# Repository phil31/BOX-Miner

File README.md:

## BOX Miner

#### The EKO-Miner is a stackable and rackable ASIC Bitcoin miner that utilizes hashcards. The hashcards are capable of mining Bitcoin by themselves or multiple. The concept of hashcards is highly scalable and offers a clean and streamlined approach to Bitcoin mining.

Miner Box Supports up to 3 ASIC Hashcards. An ATX PSU is required.

- Rackable miner boards based on specifics ASIC Hashboards, generic power supply and driven by an ESP32
- WIFI and ETHERNET connectivity
- TFT RGB LCD 172x320 display
- External standard ATX power supply
- Watercooling for quiet operation
- enclosure box dimensions: 200 x 200 x 140 mm

#### Power board : 
- designed with TPS53667 / 5 Phases / 0.5 to 2.5V, up to 380Watts
- 6 layers PCB - Outer / Inner Copper Weight: 2 oz

#### AsicBoards : 
- 16 x BM1366 : 8 TH/s - Efficiency 25J/TH
- 16 x BM1368 : 9.5 TH/s - Efficiency 18J/TH
- 10 x BM1370 : 12 TH/s - Efficiency 15J/TH

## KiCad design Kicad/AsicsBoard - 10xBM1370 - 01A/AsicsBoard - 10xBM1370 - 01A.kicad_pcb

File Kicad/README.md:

## BOX Miner

#### The EKO-Miner is a stackable and rackable ASIC Bitcoin miner that utilizes hashcards. The hashcards are capable of mining Bitcoin by themselves or multiple. The concept of hashcards is highly scalable and offers a clean and streamlined approach to Bitcoin mining.

#### 2024-12-07 : Theses boards are currently being validated

Power board : 
- designed with TPS53667 / 5 Phases / 0.5 to 2.5V, up to 300Watts

AsicBoards : 
- 16 x BM1366 : 8 TH/s - Efficiency 25J/TH
- 16 x BM1368 : 9.5 TH/s - Efficiency 18J/TH
- 10 x BM1370 : 10 TH/s - Efficiency 15J/TH

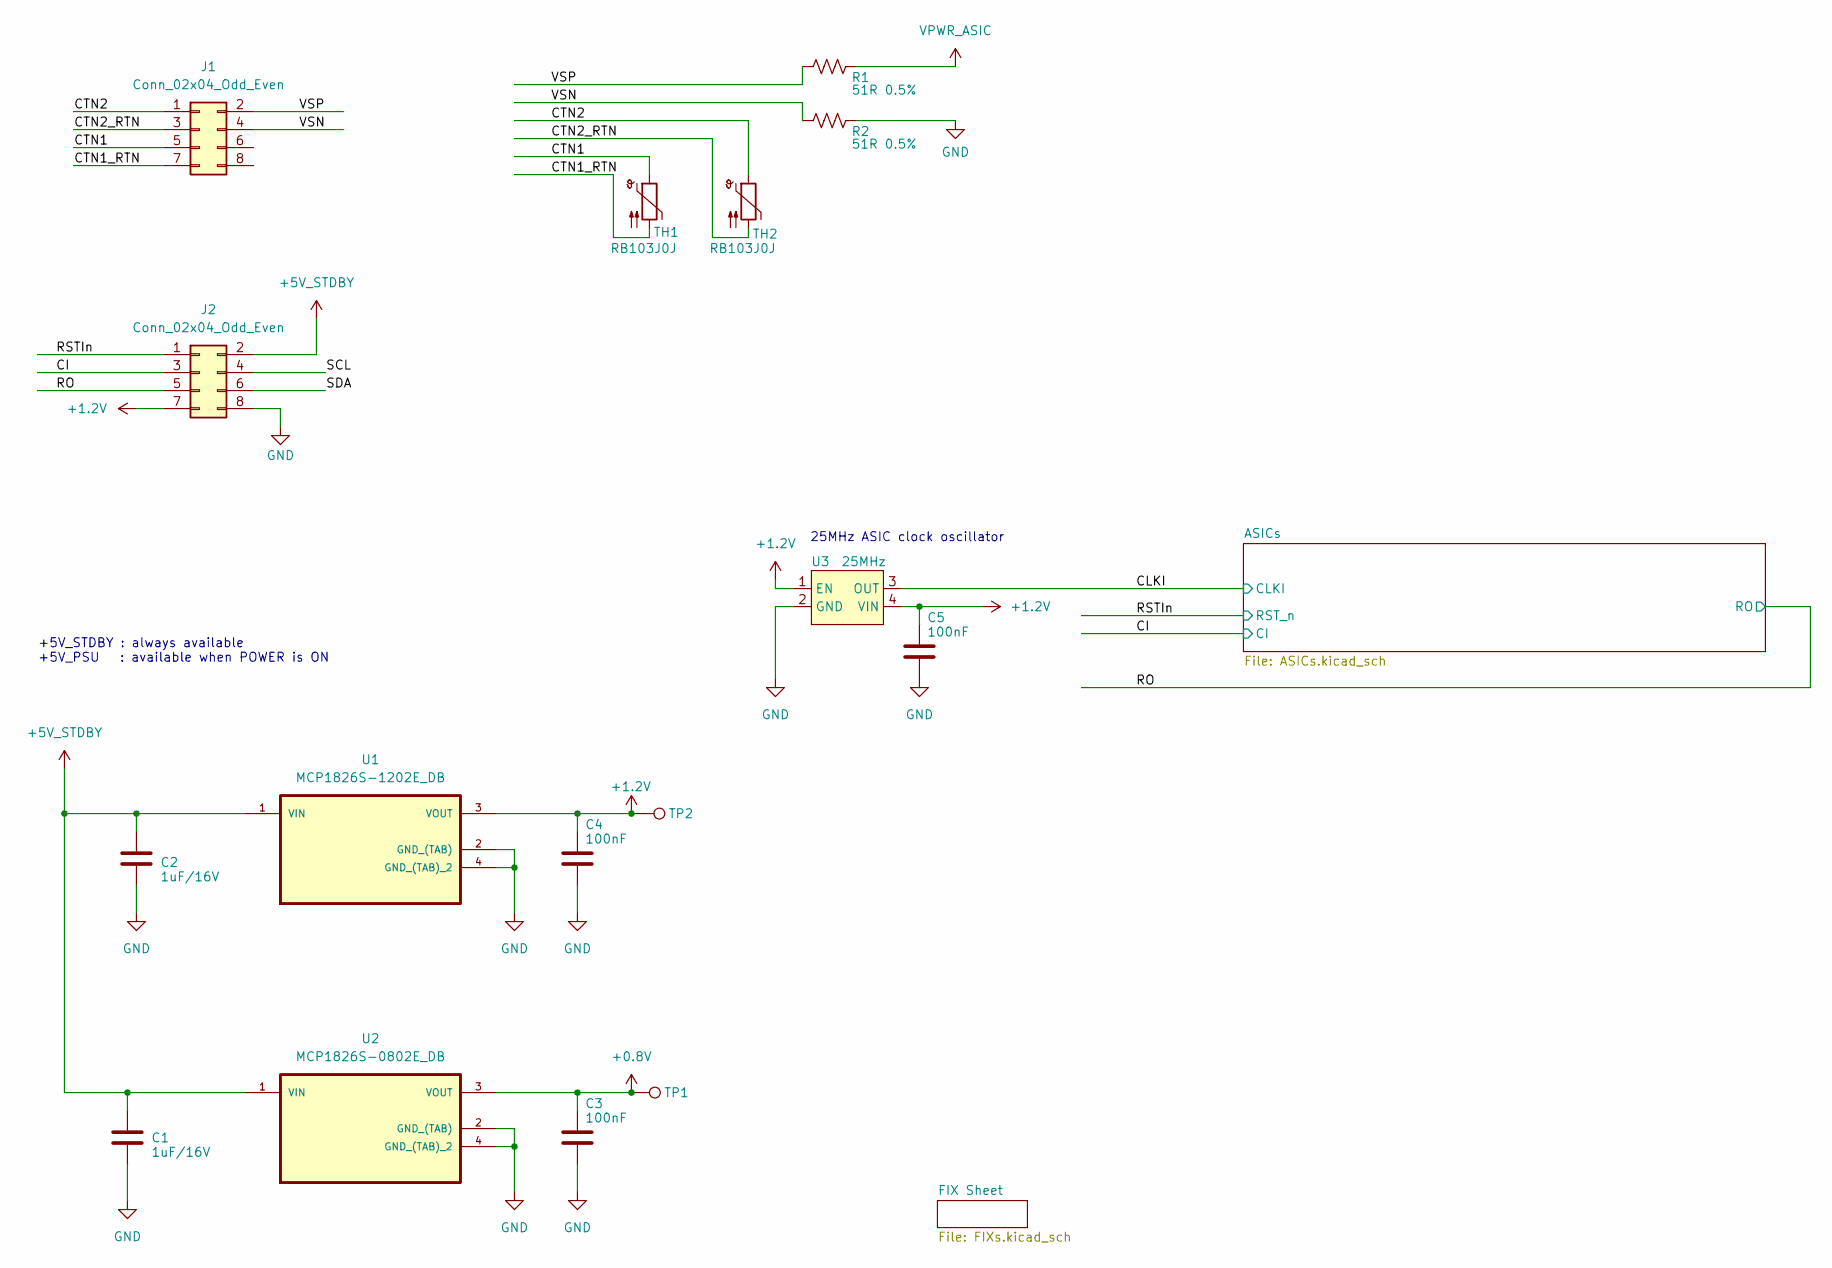
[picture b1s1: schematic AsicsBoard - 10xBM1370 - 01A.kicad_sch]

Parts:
C1, C2: 1uF/16V; C_0805_2012Metric_Pad1.18x1.45mm_HandSolder
C3, C4, C5: 100nF; C_0402_1005Metric
J1, J2: Conn_02x04_Odd_Even; PinHeader_2x04_P2.54mm_Vertical_SMD
R1, R2: 51R 0.5%; R_0805_2012Metric_Pad1.20x1.40mm_HandSolder
TH1, TH2: RB103J0J; R_0603_1608Metric
TP1, TP2: TestPoint; TestPoint_Pad_D1.0mm
U1: MCP1826S-1202E_DB; MCP1826S
U2: MCP1826S-0802E_DB; MCP1826S
U3: 25MHz; OSC_SMD_3.2x2.5mm

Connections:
+0.8V: C3.1, TP1.1, U2.3 (VOUT); also elsewhere on the board
+1.2V: C4.1, C5.1, J2.7, TP2.1, U1.3 (VOUT), U3.1 (EN), U3.4 (VIN); also elsewhere on the board
+5V_STDBY: C1.1, C2.1, J2.2, U1.1 (VIN), U2.1 (VIN)
/CI: J2.3; also elsewhere on the board
/CLKI: U3.3 (OUT); also elsewhere on the board
/CTN1: J1.5, TH1.1
/CTN1_RTN: J1.7, TH1.2
/CTN2: J1.1, TH2.1
/CTN2_RTN: J1.3, TH2.2
/RO: J2.5; also elsewhere on the board
/RSTIn: J2.1; also elsewhere on the board
/SCL: J2.4
/SDA: J2.6
/VSN: J1.4, R2.2
/VSP: J1.2, R1.2
GND: C1.2, C2.2, C3.2, C4.2, C5.2, J2.8, R2.1, U1.2 (GND_(TAB)), U1.4 (GND_(TAB)_2), U2.2 (GND_(TAB)), U2.4 (GND_(TAB)_2), U3.2 (GND); also elsewhere on the board
VPWR_ASIC: R1.1; also elsewhere on the board

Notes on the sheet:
+5V_STDBY : always available +5V_PSU : available when POWER is ON
25MHz ASIC clock oscillator

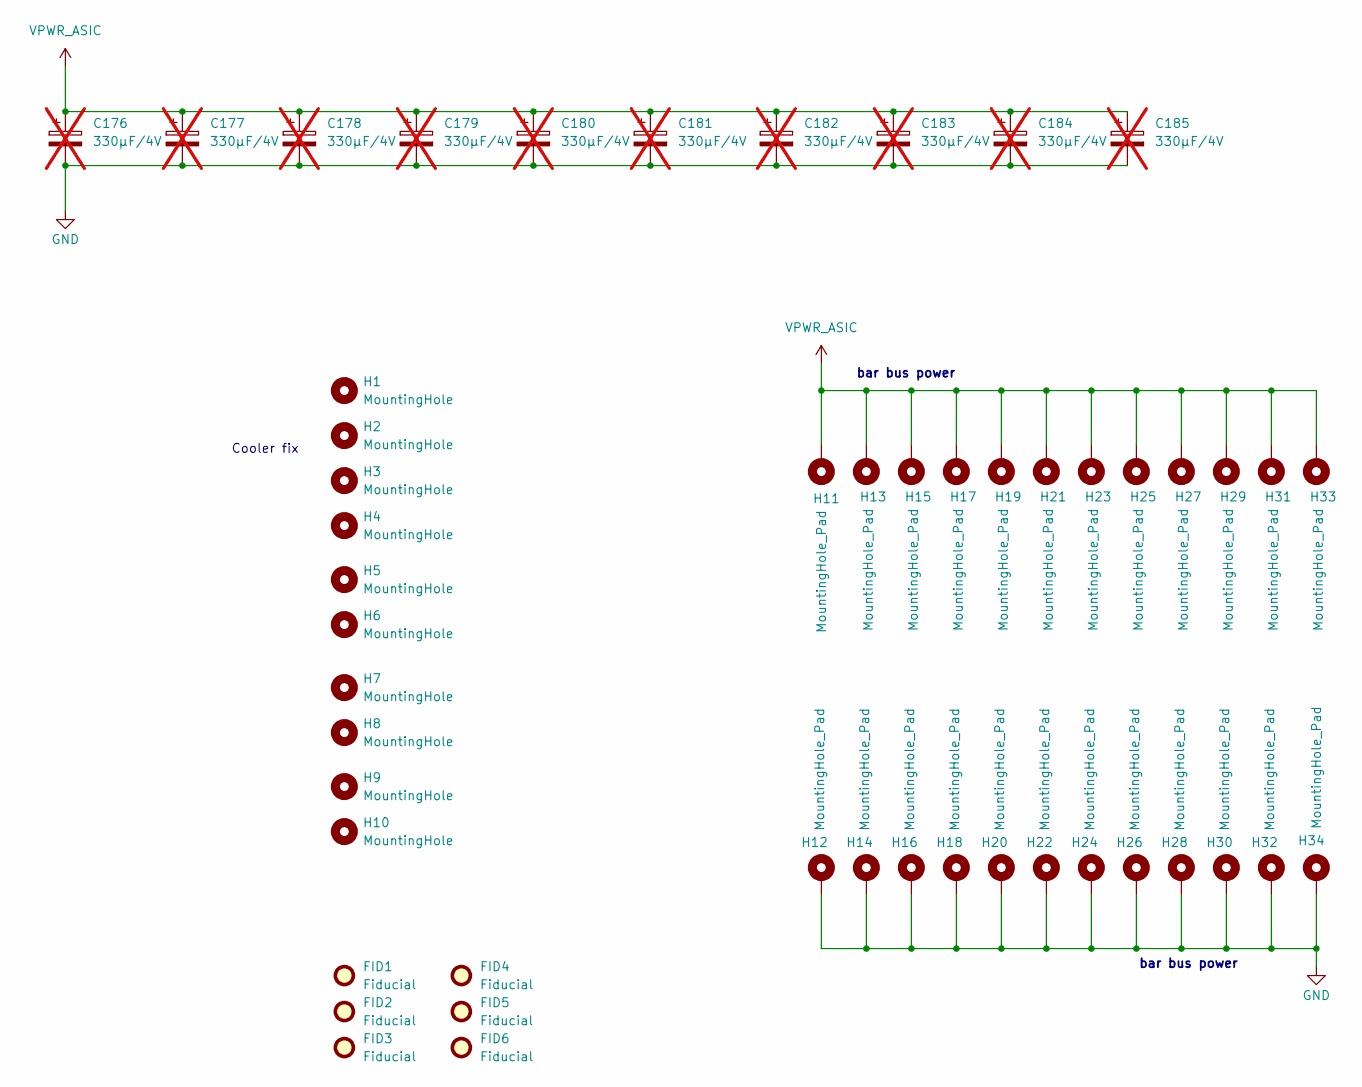
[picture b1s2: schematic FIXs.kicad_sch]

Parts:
C176, C177, C178, C179, C180, C181, C182, C183, C184, C185: 330µF/4V; C_1210_3225Metric; not fitted
FID1, FID2, FID3, FID4, FID5, FID6: Fiducial; Fiducial_1mm_Mask2mm
H1, H2, H3, H4, H5, H6, H7, H8, H9, H10: MountingHole; MountingHole_3.2mm_M3_ISO7380
H11, H12, H13, H14, H15, H16, H17, H18, H19, H20, H21, H22, H23, H24, H25, H26, H27, H28, H29, H30, H31, H32, H33, H34: MountingHole_Pad; SMTSO-M3-10ET

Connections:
GND: C176.2, C177.2, C178.2, C179.2, C180.2, C181.2, C182.2, C183.2, C184.2, C185.2, H12.1, H14.1, H16.1, H18.1, H20.1, H22.1, H24.1, H26.1, H28.1, H30.1, H32.1, H34.1; also elsewhere on the board
VPWR_ASIC: C176.1, C177.1, C178.1, C179.1, C180.1, C181.1, C182.1, C183.1, C184.1, C185.1, H11.1, H13.1, H15.1, H17.1, H19.1, H21.1, H23.1, H25.1, H27.1, H29.1, H31.1, H33.1; also elsewhere on the board

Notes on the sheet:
bar bus power
Cooler fix

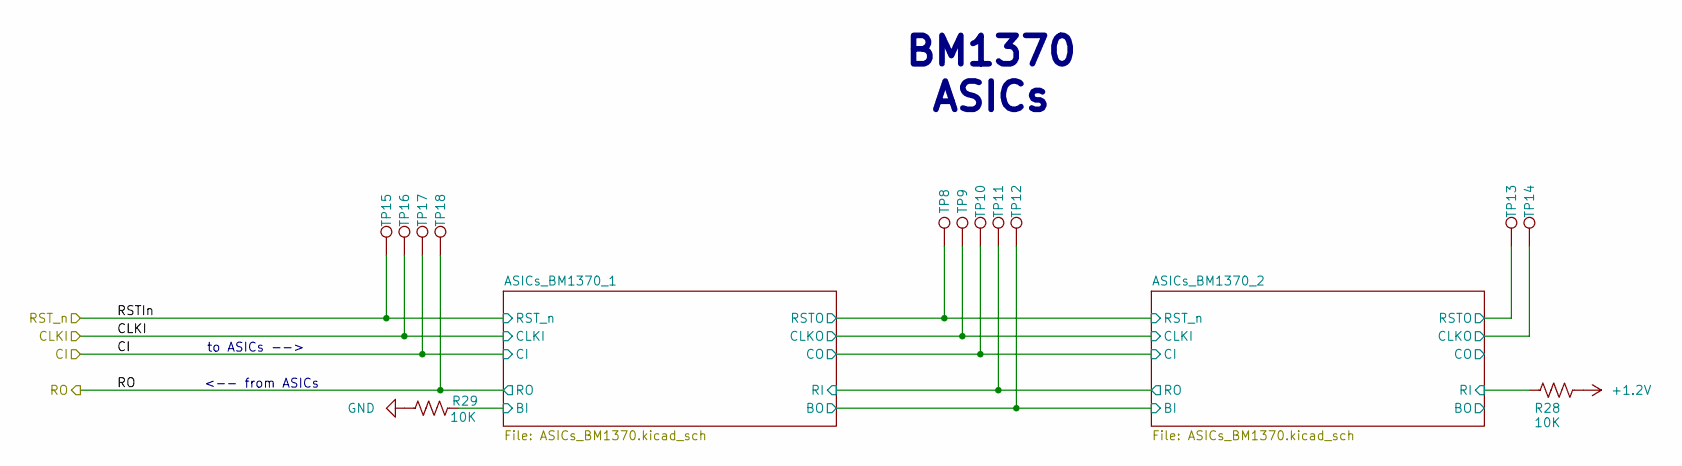
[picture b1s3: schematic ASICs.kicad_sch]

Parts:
R28, R29: 10K; R_0402_1005Metric
TP8, TP9, TP10, TP11, TP12, TP13, TP14, TP15, TP16, TP17, TP18: TestPoint; TestPoint_Pad_D1.0mm

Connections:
+1.2V: R28.1; also elsewhere on the board
/ASICs/ASICs_BM1370_1/BM1370-0/BI: R29.2; also elsewhere on the board
/ASICs/ASICs_BM1370_1/BM1370-4/BO: TP12.1; also elsewhere on the board
/ASICs/ASICs_BM1370_1/BM1370-4/CLKO: TP9.1; also elsewhere on the board
/ASICs/ASICs_BM1370_1/BM1370-4/CO: TP10.1; also elsewhere on the board
/ASICs/ASICs_BM1370_1/BM1370-4/RI: TP11.1; also elsewhere on the board
/ASICs/ASICs_BM1370_1/BM1370-4/RSTO_n: TP8.1; also elsewhere on the board
/ASICs/ASICs_BM1370_2/BM1370-4/CLKO: TP14.1; also elsewhere on the board
/ASICs/ASICs_BM1370_2/BM1370-4/RI: R28.2; also elsewhere on the board
/ASICs/ASICs_BM1370_2/BM1370-4/RSTO_n: TP13.1; also elsewhere on the board
/CI: TP17.1; also elsewhere on the board
/CLKI: TP16.1; also elsewhere on the board
/RO: TP18.1; also elsewhere on the board
/RSTIn: TP15.1; also elsewhere on the board
GND: R29.1; also elsewhere on the board

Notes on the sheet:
BM1370 ASICs
<-- from ASICs
to ASICs -->

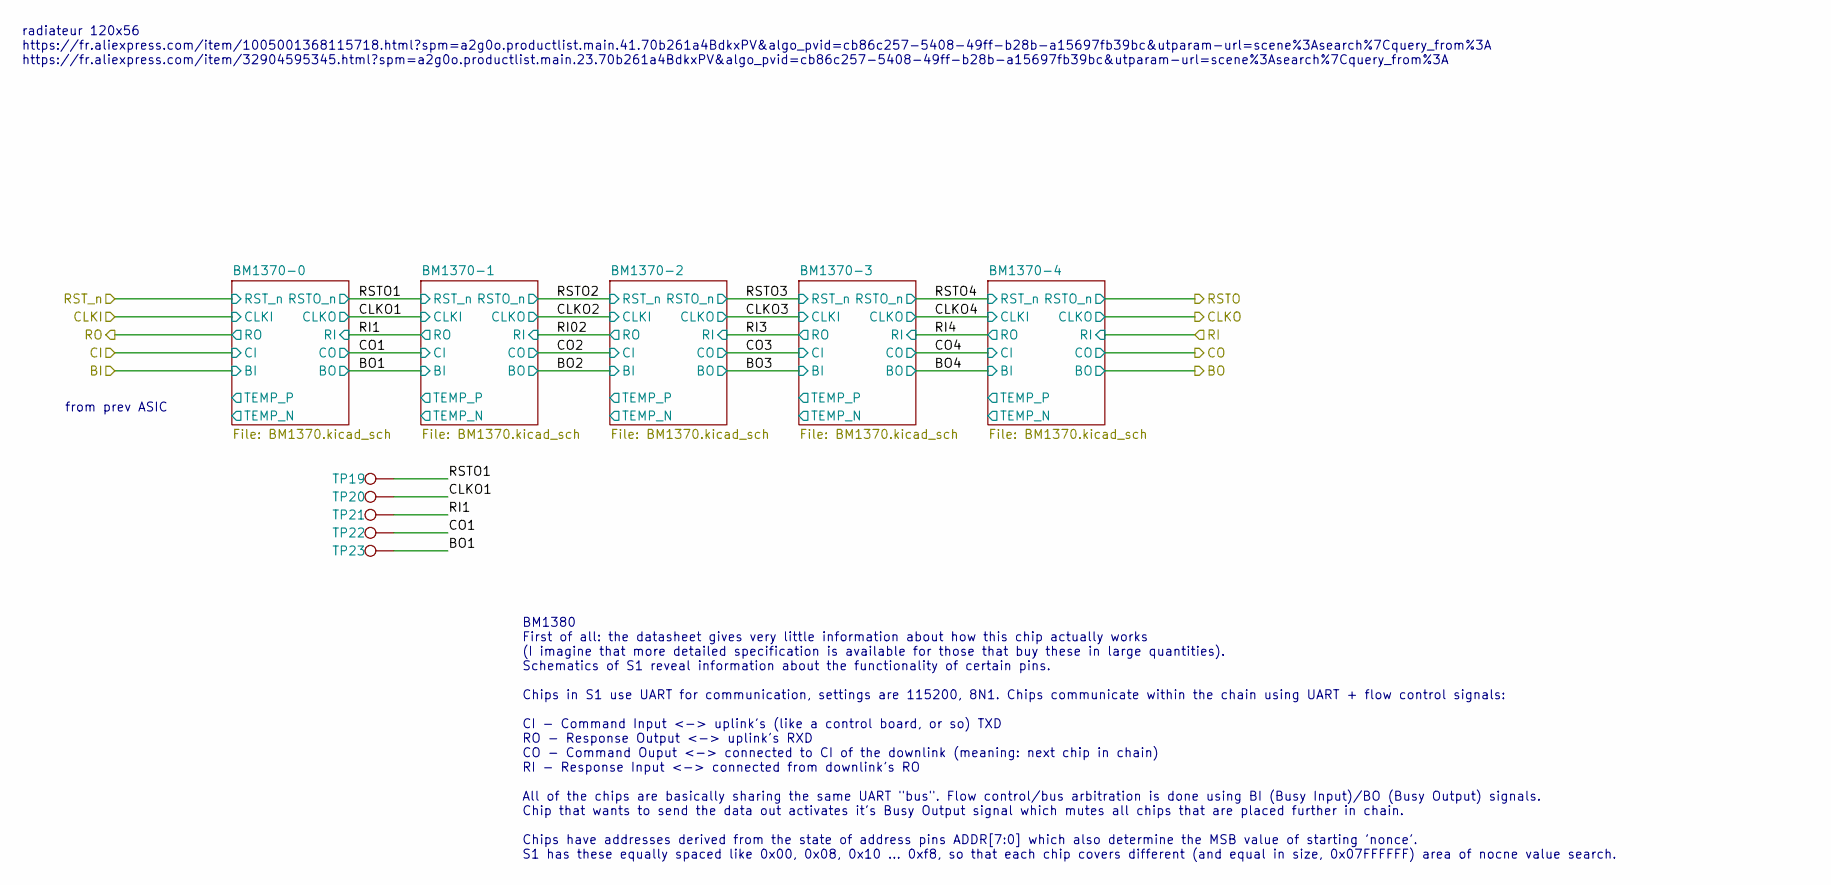
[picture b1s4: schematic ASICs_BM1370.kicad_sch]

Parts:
TP19, TP20, TP21, TP22, TP23: TestPoint; TestPoint_Pad_D1.0mm

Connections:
/ASICs/ASICs_BM1370_2/BO1: TP23.1; also elsewhere on the board
/ASICs/ASICs_BM1370_2/CLKO1: TP20.1; also elsewhere on the board
/ASICs/ASICs_BM1370_2/CO1: TP22.1; also elsewhere on the board
/ASICs/ASICs_BM1370_2/RI1: TP21.1; also elsewhere on the board
/ASICs/ASICs_BM1370_2/RSTO1: TP19.1; also elsewhere on the board

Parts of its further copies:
TP3, TP4, TP5, TP6, TP7: TestPoint; TestPoint_Pad_D1.0mm

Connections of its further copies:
/ASICs/ASICs_BM1370_1/BO1: TP7.1; also elsewhere on the board
/ASICs/ASICs_BM1370_1/CLKO1: TP4.1; also elsewhere on the board
/ASICs/ASICs_BM1370_1/CO1: TP6.1; also elsewhere on the board
/ASICs/ASICs_BM1370_1/RI1: TP5.1; also elsewhere on the board
/ASICs/ASICs_BM1370_1/RSTO1: TP3.1; also elsewhere on the board

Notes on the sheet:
from prev ASIC
BM1380 First of all: the datasheet gives very little information about how this chip actually works (I imagine that more detailed specification is available for those that buy these in large quantities). Schematics of S1 reveal information about the functionality of certain pins. Chips in S1 use UA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
radiateur 120x56 https://fr.aliexpress.com/item/1005001368115718.html?spm=a2g0o.productlist.main.41.70b261a4BdkxPV&algo_pvid=cb86c257-5408-49ff-b28b-a15697fb39bc&utparam-url=scene%3Asearch%7Cquery_from%3A https://fr.aliexpress.com/item/32904595345.html?spm=a2g0o.productlist.main.23.70b261a4BdkxPV&a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

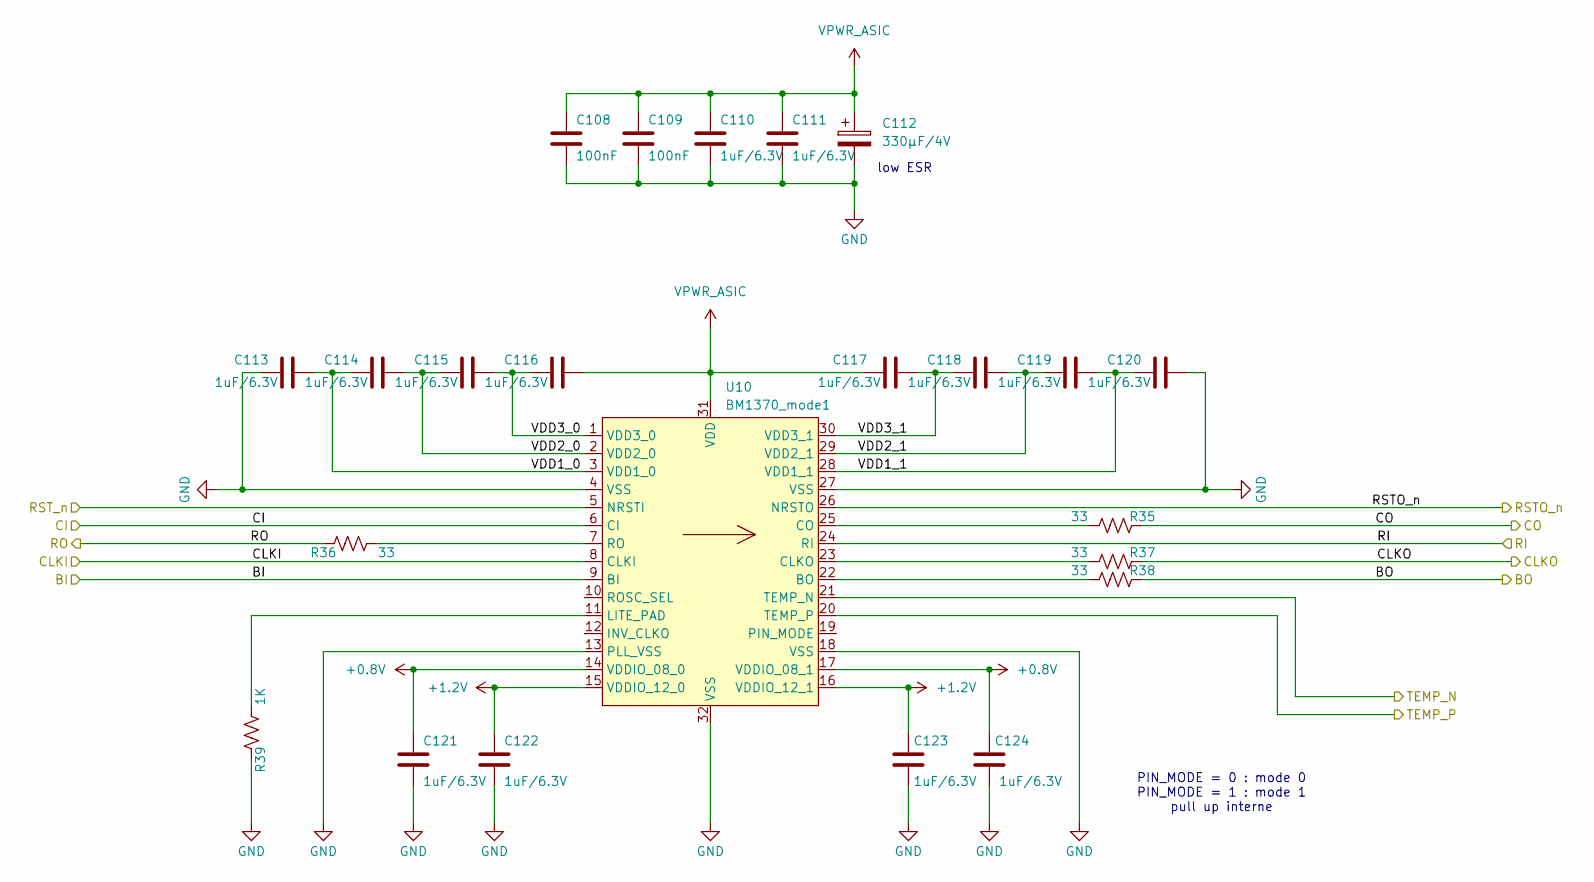
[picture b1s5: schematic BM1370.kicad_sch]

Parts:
C108, C109: 100nF; C_0402_1005Metric
C110, C111, C113, C114, C115, C116, C117, C118, C119, C120, C121, C122, C123, C124: 1uF/6.3V; C_0402_1005Metric
C112: 330µF/4V; C_1210_3225Metric
R35, R36, R37, R38: 33; R_0402_1005Metric
R39: 1K; R_0402_1005Metric
U10: BM1370_mode1; BM1370

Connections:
+0.8V: C121.1, C124.1, U10.14 (VDDIO_08_0), U10.17 (VDDIO_08_1); also elsewhere on the board
+1.2V: C122.1, C123.1, U10.15 (VDDIO_12_0), U10.16 (VDDIO_12_1); also elsewhere on the board
/ASICs/ASICs_BM1370_1/BM1370-4/BO: U10.9 (BI); also elsewhere on the board
/ASICs/ASICs_BM1370_1/BM1370-4/CLKO: U10.8 (CLKI); also elsewhere on the board
/ASICs/ASICs_BM1370_1/BM1370-4/CO: U10.6 (CI); also elsewhere on the board
/ASICs/ASICs_BM1370_1/BM1370-4/RI: R36.2; also elsewhere on the board
/ASICs/ASICs_BM1370_1/BM1370-4/RSTO_n: U10.5 (NRSTI); also elsewhere on the board
/ASICs/ASICs_BM1370_2/BM1370-0/TEMP_N: U10.21 (TEMP_N)
/ASICs/ASICs_BM1370_2/BM1370-0/TEMP_P: U10.20 (TEMP_P)
/ASICs/ASICs_BM1370_2/BM1370-0/VDD1_0: C113.2, C114.1, U10.3 (VDD1_0)
/ASICs/ASICs_BM1370_2/BM1370-0/VDD1_1: C119.2, C120.1, U10.28 (VDD1_1)
/ASICs/ASICs_BM1370_2/BM1370-0/VDD2_0: C114.2, C115.1, U10.2 (VDD2_0)
/ASICs/ASICs_BM1370_2/BM1370-0/VDD2_1: C118.2, C119.1, U10.29 (VDD2_1)
/ASICs/ASICs_BM1370_2/BM1370-0/VDD3_0: C115.2, C116.1, U10.1 (VDD3_0)
/ASICs/ASICs_BM1370_2/BM1370-0/VDD3_1: C117.2, C118.1, U10.30 (VDD3_1)
/ASICs/ASICs_BM1370_2/BO1: R38.2; also elsewhere on the board
/ASICs/ASICs_BM1370_2/CLKO1: R37.2; also elsewhere on the board
/ASICs/ASICs_BM1370_2/CO1: R35.2; also elsewhere on the board
/ASICs/ASICs_BM1370_2/RI1: U10.24 (RI); also elsewhere on the board
/ASICs/ASICs_BM1370_2/RSTO1: U10.26 (NRSTO); also elsewhere on the board
GND: C108.2, C109.2, C110.2, C111.2, C112.2, C113.1, C120.2, C121.2, C122.2, C123.2, C124.2, R39.2, U10.4 (VSS), U10.13 (PLL_VSS), U10.18 (VSS), U10.27 (VSS), U10.32 (VSS); also elsewhere on the board
unnamed: R38.1, U10.22 (BO)
unnamed: R37.1, U10.23 (CLKO)
unnamed: R35.1, U10.25 (CO)
unnamed: R39.1, U10.11 (LITE_PAD)
unnamed: R36.1, U10.7 (RO)
VPWR_ASIC: C108.1, C109.1, C110.1, C111.1, C112.1, C116.2, C117.1, U10.31 (VDD); also elsewhere on the board

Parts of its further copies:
C6, C7, C23, C24, C40, C41, C57, C58, C74, C75, C91, C92, C125, C126, C142, C143, C159, C160: 100nF; C_0402_1005Metric
C8, C9, C11, C12, C13, C14, C15, C16, C17, C18, C19, C20, C21, C22, C25, C26, C28, C29, C30, C31, C32, C33, C34, C35, C36, C37, C38, C39, C42, C43, C45, C46, C47, C48, C49, C50, C51, C52, C53, C54, C55, C56, C59, C60, C62, C63, C64, C65, C66, C67, C68, C69, C70, C71, C72, C73, C76, C77, C79, C80, C81, C82, C83, C84, C85, C86, C87, C88, C89, C90, C93, C94, C96, C97, C98, C99, C100, C101, C102, C103, C104, C105, C106, C107, C127, C128, C130, C131, C132, C133, C134, C135, C136, C137, C138, C139, C140, C141, C144, C145, C147, C148, C149, C150, C151, C152, C153, C154, C155, C156, C157, C158, C161, C162, C164, C165, C166, C167, C168, C169, C170, C171, C172, C173, C174, C175: 1uF/6.3V; C_0402_1005Metric
C10, C27, C44, C61, C78, C95, C129, C146, C163: 330µF/4V; C_1210_3225Metric
R3, R4, R5, R6, R8, R9, R10, R11, R13, R14, R15, R16, R18, R19, R20, R21, R23, R24, R25, R26, R30, R31, R32, R33, R40, R41, R42, R43, R45, R46, R47, R48, R50, R51, R52, R53: 33; R_0402_1005Metric
R7, R12, R17, R22, R27, R34, R44, R49, R54: 1K; R_0402_1005Metric
U4, U5, U6, U7, U8, U9, U11, U12, U13: BM1370_mode1; BM1370

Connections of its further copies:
+0.8V: C19.1, C22.1, C36.1, C39.1, C53.1, C56.1, C70.1, C73.1, C87.1, C90.1, C104.1, C107.1, C138.1, C141.1, C155.1, C158.1, C172.1, C175.1, U4.14 (VDDIO_08_0), U4.17 (VDDIO_08_1), U5.14 (VDDIO_08_0), U5.17 (VDDIO_08_1), U6.14 (VDDIO_08_0), U6.17 (VDDIO_08_1), U7.14 (VDDIO_08_0), U7.17 (VDDIO_08_1), U8.14 (VDDIO_08_0), U8.17 (VDDIO_08_1), U9.14 (VDDIO_08_0), U9.17 (VDDIO_08_1), U11.14 (VDDIO_08_0), U11.17 (VDDIO_08_1), U12.14 (VDDIO_08_0), U12.17 (VDDIO_08_1), U13.14 (VDDIO_08_0), U13.17 (VDDIO_08_1); also elsewhere on the board
+1.2V: C20.1, C21.1, C37.1, C38.1, C54.1, C55.1, C71.1, C72.1, C88.1, C89.1, C105.1, C106.1, C139.1, C140.1, C156.1, C157.1, C173.1, C174.1, U4.15 (VDDIO_12_0), U4.16 (VDDIO_12_1), U5.15 (VDDIO_12_0), U5.16 (VDDIO_12_1), U6.15 (VDDIO_12_0), U6.16 (VDDIO_12_1), U7.15 (VDDIO_12_0), U7.16 (VDDIO_12_1), U8.15 (VDDIO_12_0), U8.16 (VDDIO_12_1), U9.15 (VDDIO_12_0), U9.16 (VDDIO_12_1), U11.15 (VDDIO_12_0), U11.16 (VDDIO_12_1), U12.15 (VDDIO_12_0), U12.16 (VDDIO_12_1), U13.15 (VDDIO_12_0), U13.16 (VDDIO_12_1); also elsewhere on the board
/ASICs/ASICs_BM1370_1/BM1370-0/BI: U5.9 (BI); also elsewhere on the board
/ASICs/ASICs_BM1370_1/BM1370-0/TEMP_N: U5.21 (TEMP_N)
/ASICs/ASICs_BM1370_1/BM1370-0/TEMP_P: U5.20 (TEMP_P)
/ASICs/ASICs_BM1370_1/BM1370-0/VDD1_0: C28.2, C29.1, U5.3 (VDD1_0)
/ASICs/ASICs_BM1370_1/BM1370-0/VDD1_1: C34.2, C35.1, U5.28 (VDD1_1)
/ASICs/ASICs_BM1370_1/BM1370-0/VDD2_0: C29.2, C30.1, U5.2 (VDD2_0)
/ASICs/ASICs_BM1370_1/BM1370-0/VDD2_1: C33.2, C34.1, U5.29 (VDD2_1)
/ASICs/ASICs_BM1370_1/BM1370-0/VDD3_0: C30.2, C31.1, U5.1 (VDD3_0)
/ASICs/ASICs_BM1370_1/BM1370-0/VDD3_1: C32.2, C33.1, U5.30 (VDD3_1)
/ASICs/ASICs_BM1370_1/BM1370-1/TEMP_N: U4.21 (TEMP_N)
/ASICs/ASICs_BM1370_1/BM1370-1/TEMP_P: U4.20 (TEMP_P)
/ASICs/ASICs_BM1370_1/BM1370-1/VDD1_0: C11.2, C12.1, U4.3 (VDD1_0)
/ASICs/ASICs_BM1370_1/BM1370-1/VDD1_1: C17.2, C18.1, U4.28 (VDD1_1)
/ASICs/ASICs_BM1370_1/BM1370-1/VDD2_0: C12.2, C13.1, U4.2 (VDD2_0)
/ASICs/ASICs_BM1370_1/BM1370-1/VDD2_1: C16.2, C17.1, U4.29 (VDD2_1)
/ASICs/ASICs_BM1370_1/BM1370-1/VDD3_0: C13.2, C14.1, U4.1 (VDD3_0)
/ASICs/ASICs_BM1370_1/BM1370-1/VDD3_1: C15.2, C16.1, U4.30 (VDD3_1)
/ASICs/ASICs_BM1370_1/BM1370-2/TEMP_N: U7.21 (TEMP_N)
/ASICs/ASICs_BM1370_1/BM1370-2/TEMP_P: U7.20 (TEMP_P)
/ASICs/ASICs_BM1370_1/BM1370-2/VDD1_0: C62.2, C63.1, U7.3 (VDD1_0)
/ASICs/ASICs_BM1370_1/BM1370-2/VDD1_1: C68.2, C69.1, U7.28 (VDD1_1)
/ASICs/ASICs_BM1370_1/BM1370-2/VDD2_0: C63.2, C64.1, U7.2 (VDD2_0)
/ASICs/ASICs_BM1370_1/BM1370-2/VDD2_1: C67.2, C68.1, U7.29 (VDD2_1)
/ASICs/ASICs_BM1370_1/BM1370-2/VDD3_0: C64.2, C65.1, U7.1 (VDD3_0)
/ASICs/ASICs_BM1370_1/BM1370-2/VDD3_1: C66.2, C67.1, U7.30 (VDD3_1)
/ASICs/ASICs_BM1370_1/BM1370-3/TEMP_N: U9.21 (TEMP_N)
/ASICs/ASICs_BM1370_1/BM1370-3/TEMP_P: U9.20 (TEMP_P)
/ASICs/ASICs_BM1370_1/BM1370-3/VDD1_0: C96.2, C97.1, U9.3 (VDD1_0)
/ASICs/ASICs_BM1370_1/BM1370-3/VDD1_1: C102.2, C103.1, U9.28 (VDD1_1)
/ASICs/ASICs_BM1370_1/BM1370-3/VDD2_0: C97.2, C98.1, U9.2 (VDD2_0)
/ASICs/ASICs_BM1370_1/BM1370-3/VDD2_1: C101.2, C102.1, U9.29 (VDD2_1)
/ASICs/ASICs_BM1370_1/BM1370-3/VDD3_0: C98.2, C99.1, U9.1 (VDD3_0)
/ASICs/ASICs_BM1370_1/BM1370-3/VDD3_1: C100.2, C101.1, U9.30 (VDD3_1)
/ASICs/ASICs_BM1370_1/BM1370-4/BO: R48.2; also elsewhere on the board
/ASICs/ASICs_BM1370_1/BM1370-4/CLKO: R47.2; also elsewhere on the board
/ASICs/ASICs_BM1370_1/BM1370-4/CO: R45.2; also elsewhere on the board
/ASICs/ASICs_BM1370_1/BM1370-4/RI: U12.24 (RI); also elsewhere on the board
/ASICs/ASICs_BM1370_1/BM1370-4/RSTO_n: U12.26 (NRSTO); also elsewhere on the board
/ASICs/ASICs_BM1370_1/BM1370-4/TEMP_N: U12.21 (TEMP_N)
/ASICs/ASICs_BM1370_1/BM1370-4/TEMP_P: U12.20 (TEMP_P)
/ASICs/ASICs_BM1370_1/BM1370-4/VDD1_0: C147.2, C148.1, U12.3 (VDD1_0)
/ASICs/ASICs_BM1370_1/BM1370-4/VDD1_1: C153.2, C154.1, U12.28 (VDD1_1)
/ASICs/ASICs_BM1370_1/BM1370-4/VDD2_0: C148.2, C149.1, U12.2 (VDD2_0)
/ASICs/ASICs_BM1370_1/BM1370-4/VDD2_1: C152.2, C153.1, U12.29 (VDD2_1)
/ASICs/ASICs_BM1370_1/BM1370-4/VDD3_0: C149.2, C150.1, U12.1 (VDD3_0)
/ASICs/ASICs_BM1370_1/BM1370-4/VDD3_1: C151.2, C152.1, U12.30 (VDD3_1)
/ASICs/ASICs_BM1370_1/BO1: R11.2, U4.9 (BI); also elsewhere on the board
/ASICs/ASICs_BM1370_1/BO2: R6.2, U7.9 (BI)
/ASICs/ASICs_BM1370_1/BO3: R21.2, U9.9 (BI)
/ASICs/ASICs_BM1370_1/BO4: R33.2, U12.9 (BI)
/ASICs/ASICs_BM1370_1/CLKO1: R10.2, U4.8 (CLKI); also elsewhere on the board
/ASICs/ASICs_BM1370_1/CLKO2: R5.2, U7.8 (CLKI)
/ASICs/ASICs_BM1370_1/CLKO3: R20.2, U9.8 (CLKI)
/ASICs/ASICs_BM1370_1/CLKO4: R32.2, U12.8 (CLKI)
/ASICs/ASICs_BM1370_1/CO1: R8.2, U4.6 (CI); also elsewhere on the board
/ASICs/ASICs_BM1370_1/CO2: R3.2, U7.6 (CI)
/ASICs/ASICs_BM1370_1/CO3: R18.2, U9.6 (CI)
/ASICs/ASICs_BM1370_1/CO4: R30.2, U12.6 (CI)
/ASICs/ASICs_BM1370_1/RI1: R4.2, U5.24 (RI); also elsewhere on the board
/ASICs/ASICs_BM1370_1/RI02: R19.2, U4.24 (RI)
/ASICs/ASICs_BM1370_1/RI3: R31.2, U7.24 (RI)
/ASICs/ASICs_BM1370_1/RI4: R46.2, U9.24 (RI)
/ASICs/ASICs_BM1370_1/RSTO1: U4.5 (NRSTI), U5.26 (NRSTO); also elsewhere on the board
/ASICs/ASICs_BM1370_1/RSTO2: U4.26 (NRSTO), U7.5 (NRSTI)
/ASICs/ASICs_BM1370_1/RSTO3: U7.26 (NRSTO), U9.5 (NRSTI)
/ASICs/ASICs_BM1370_1/RSTO4: U9.26 (NRSTO), U12.5 (NRSTI)
/ASICs/ASICs_BM1370_2/BM1370-1/TEMP_N: U6.21 (TEMP_N)
/ASICs/ASICs_BM1370_2/BM1370-1/TEMP_P: U6.20 (TEMP_P)
/ASICs/ASICs_BM1370_2/BM1370-1/VDD1_0: C45.2, C46.1, U6.3 (VDD1_0)
/ASICs/ASICs_BM1370_2/BM1370-1/VDD1_1: C51.2, C52.1, U6.28 (VDD1_1)
/ASICs/ASICs_BM1370_2/BM1370-1/VDD2_0: C46.2, C47.1, U6.2 (VDD2_0)
/ASICs/ASICs_BM1370_2/BM1370-1/VDD2_1: C50.2, C51.1, U6.29 (VDD2_1)
/ASICs/ASICs_BM1370_2/BM1370-1/VDD3_0: C47.2, C48.1, U6.1 (VDD3_0)
/ASICs/ASICs_BM1370_2/BM1370-1/VDD3_1: C49.2, C50.1, U6.30 (VDD3_1)
/ASICs/ASICs_BM1370_2/BM1370-2/TEMP_N: U8.21 (TEMP_N)
/ASICs/ASICs_BM1370_2/BM1370-2/TEMP_P: U8.20 (TEMP_P)
/ASICs/ASICs_BM1370_2/BM1370-2/VDD1_0: C79.2, C80.1, U8.3 (VDD1_0)
/ASICs/ASICs_BM1370_2/BM1370-2/VDD1_1: C85.2, C86.1, U8.28 (VDD1_1)
/ASICs/ASICs_BM1370_2/BM1370-2/VDD2_0: C80.2, C81.1, U8.2 (VDD2_0)
/ASICs/ASICs_BM1370_2/BM1370-2/VDD2_1: C84.2, C85.1, U8.29 (VDD2_1)
/ASICs/ASICs_BM1370_2/BM1370-2/VDD3_0: C81.2, C82.1, U8.1 (VDD3_0)
/ASICs/ASICs_BM1370_2/BM1370-2/VDD3_1: C83.2, C84.1, U8.30 (VDD3_1)
/ASICs/ASICs_BM1370_2/BM1370-3/TEMP_N: U11.21 (TEMP_N)
/ASICs/ASICs_BM1370_2/BM1370-3/TEMP_P: U11.20 (TEMP_P)
/ASICs/ASICs_BM1370_2/BM1370-3/VDD1_0: C130.2, C131.1, U11.3 (VDD1_0)
/ASICs/ASICs_BM1370_2/BM1370-3/VDD1_1: C136.2, C137.1, U11.28 (VDD1_1)
/ASICs/ASICs_BM1370_2/BM1370-3/VDD2_0: C131.2, C132.1, U11.2 (VDD2_0)
/ASICs/ASICs_BM1370_2/BM1370-3/VDD2_1: C135.2, C136.1, U11.29 (VDD2_1)
/ASICs/ASICs_BM1370_2/BM1370-3/VDD3_0: C132.2, C133.1, U11.1 (VDD3_0)
/ASICs/ASICs_BM1370_2/BM1370-3/VDD3_1: C134.2, C135.1, U11.30 (VDD3_1)
/ASICs/ASICs_BM1370_2/BM1370-4/BO: R53.2
/ASICs/ASICs_BM1370_2/BM1370-4/CLKO: R52.2; also elsewhere on the board
/ASICs/ASICs_BM1370_2/BM1370-4/CO: R50.2
/ASICs/ASICs_BM1370_2/BM1370-4/RI: U13.24 (RI); also elsewhere on the board
/ASICs/ASICs_BM1370_2/BM1370-4/RSTO_n: U13.26 (NRSTO); also elsewhere on the board
/ASICs/ASICs_BM1370_2/BM1370-4/TEMP_N: U13.21 (TEMP_N)
/ASICs/ASICs_BM1370_2/BM1370-4/TEMP_P: U13.20 (TEMP_P)
/ASICs/ASICs_BM1370_2/BM1370-4/VDD1_0: C164.2, C165.1, U13.3 (VDD1_0)
/ASICs/ASICs_BM1370_2/BM1370-4/VDD1_1: C170.2, C171.1, U13.28 (VDD1_1)
/ASICs/ASICs_BM1370_2/BM1370-4/VDD2_0: C165.2, C166.1, U13.2 (VDD2_0)
/ASICs/ASICs_BM1370_2/BM1370-4/VDD2_1: C169.2, C170.1, U13.29 (VDD2_1)
/ASICs/ASICs_BM1370_2/BM1370-4/VDD3_0: C166.2, C167.1, U13.1 (VDD3_0)
/ASICs/ASICs_BM1370_2/BM1370-4/VDD3_1: C168.2, C169.1, U13.30 (VDD3_1)
/ASICs/ASICs_BM1370_2/BO1: U6.9 (BI); also elsewhere on the board
/ASICs/ASICs_BM1370_2/BO2: R16.2, U8.9 (BI)
/ASICs/ASICs_BM1370_2/BO3: R26.2, U11.9 (BI)
/ASICs/ASICs_BM1370_2/BO4: R43.2, U13.9 (BI)
/ASICs/ASICs_BM1370_2/CLKO1: U6.8 (CLKI); also elsewhere on the board
/ASICs/ASICs_BM1370_2/CLKO2: R15.2, U8.8 (CLKI)
/ASICs/ASICs_BM1370_2/CLKO3: R25.2, U11.8 (CLKI)
/ASICs/ASICs_BM1370_2/CLKO4: R42.2, U13.8 (CLKI)
/ASICs/ASICs_BM1370_2/CO1: U6.6 (CI); also elsewhere on the board
/ASICs/ASICs_BM1370_2/CO2: R13.2, U8.6 (CI)
/ASICs/ASICs_BM1370_2/CO3: R23.2, U11.6 (CI)
/ASICs/ASICs_BM1370_2/CO4: R40.2, U13.6 (CI)
/ASICs/ASICs_BM1370_2/RI1: R14.2; also elsewhere on the board
/ASICs/ASICs_BM1370_2/RI02: R24.2, U6.24 (RI)
/ASICs/ASICs_BM1370_2/RI3: R41.2, U8.24 (RI)
/ASICs/ASICs_BM1370_2/RI4: R51.2, U11.24 (RI)
/ASICs/ASICs_BM1370_2/RSTO1: U6.5 (NRSTI); also elsewhere on the board
/ASICs/ASICs_BM1370_2/RSTO2: U6.26 (NRSTO), U8.5 (NRSTI)
/ASICs/ASICs_BM1370_2/RSTO3: U8.26 (NRSTO), U11.5 (NRSTI)
/ASICs/ASICs_BM1370_2/RSTO4: U11.26 (NRSTO), U13.5 (NRSTI)
/CI: U5.6 (CI); also elsewhere on the board
/CLKI: U5.8 (CLKI); also elsewhere on the board
/RO: R9.2; also elsewhere on the board
/RSTIn: U5.5 (NRSTI); also elsewhere on the board
GND: C6.2, C7.2, C8.2, C9.2, C10.2, C11.1, C18.2, C19.2, C20.2, C21.2, C22.2, C23.2, C24.2, C25.2, C26.2, C27.2, C28.1, C35.2, C36.2, C37.2, C38.2, C39.2, C40.2, C41.2, C42.2, C43.2, C44.2, C45.1, C52.2, C53.2, C54.2, C55.2, C56.2, C57.2, C58.2, C59.2, C60.2, C61.2, C62.1, C69.2, C70.2, C71.2, C72.2, C73.2, C74.2, C75.2, C76.2, C77.2, C78.2, C79.1, C86.2, C87.2, C88.2, C89.2, C90.2, C91.2, C92.2, C93.2, C94.2, C95.2, C96.1, C103.2, C104.2, C105.2, C106.2, C107.2, C125.2, C126.2, C127.2, C128.2, C129.2, C130.1, C137.2, C138.2, C139.2, C140.2, C141.2, C142.2, C143.2, C144.2, C145.2, C146.2, C147.1, C154.2, C155.2, C156.2, C157.2, C158.2, C159.2, C160.2, C161.2, C162.2, C163.2, C164.1, C171.2, C172.2, C173.2, C174.2, C175.2, R7.2, R12.2, R17.2, R22.2, R27.2, R34.2, R44.2, R49.2, R54.2, U4.4 (VSS), U4.13 (PLL_VSS), U4.18 (VSS), U4.27 (VSS), U4.32 (VSS), U5.4 (VSS), U5.13 (PLL_VSS), U5.18 (VSS), U5.27 (VSS), U5.32 (VSS), U6.4 (VSS), U6.13 (PLL_VSS), U6.18 (VSS), U6.27 (VSS), U6.32 (VSS), U7.4 (VSS), U7.13 (PLL_VSS), U7.18 (VSS), U7.27 (VSS), U7.32 (VSS), U8.4 (VSS), U8.13 (PLL_VSS), U8.18 (VSS), U8.27 (VSS), U8.32 (VSS), U9.4 (VSS), U9.13 (PLL_VSS), U9.18 (VSS), U9.27 (VSS), U9.32 (VSS), U11.4 (VSS), U11.13 (PLL_VSS), U11.18 (VSS), U11.27 (VSS), U11.32 (VSS), U12.4 (VSS), U12.13 (PLL_VSS), U12.18 (VSS), U12.27 (VSS), U12.32 (VSS), U13.4 (VSS), U13.13 (PLL_VSS), U13.18 (VSS), U13.27 (VSS), U13.32 (VSS); also elsewhere on the board
unnamed: R6.1, U4.22 (BO)
unnamed: R5.1, U4.23 (CLKO)
unnamed: R3.1, U4.25 (CO)
unnamed: R7.1, U4.11 (LITE_PAD)
unnamed: R4.1, U4.7 (RO)
unnamed: R11.1, U5.22 (BO)
unnamed: R10.1, U5.23 (CLKO)
unnamed: R8.1, U5.25 (CO)
unnamed: R12.1, U5.11 (LITE_PAD)
unnamed: R9.1, U5.7 (RO)
unnamed: R16.1, U6.22 (BO)
unnamed: R15.1, U6.23 (CLKO)
unnamed: R13.1, U6.25 (CO)
unnamed: R17.1, U6.11 (LITE_PAD)
unnamed: R14.1, U6.7 (RO)
unnamed: R21.1, U7.22 (BO)
unnamed: R20.1, U7.23 (CLKO)
unnamed: R18.1, U7.25 (CO)
unnamed: R22.1, U7.11 (LITE_PAD)
unnamed: R19.1, U7.7 (RO)
unnamed: R26.1, U8.22 (BO)
unnamed: R25.1, U8.23 (CLKO)
unnamed: R23.1, U8.25 (CO)
unnamed: R27.1, U8.11 (LITE_PAD)
unnamed: R24.1, U8.7 (RO)
unnamed: R33.1, U9.22 (BO)
unnamed: R32.1, U9.23 (CLKO)
unnamed: R30.1, U9.25 (CO)
unnamed: R34.1, U9.11 (LITE_PAD)
unnamed: R31.1, U9.7 (RO)
unnamed: R43.1, U11.22 (BO)
unnamed: R42.1, U11.23 (CLKO)
unnamed: R40.1, U11.25 (CO)
unnamed: R44.1, U11.11 (LITE_PAD)
unnamed: R41.1, U11.7 (RO)
unnamed: R48.1, U12.22 (BO)
unnamed: R47.1, U12.23 (CLKO)
unnamed: R45.1, U12.25 (CO)
unnamed: R49.1, U12.11 (LITE_PAD)
unnamed: R46.1, U12.7 (RO)
unnamed: R53.1, U13.22 (BO)
unnamed: R52.1, U13.23 (CLKO)
unnamed: R50.1, U13.25 (CO)
unnamed: R54.1, U13.11 (LITE_PAD)
unnamed: R51.1, U13.7 (RO)
VPWR_ASIC: C6.1, C7.1, C8.1, C9.1, C10.1, C14.2, C15.1, C23.1, C24.1, C25.1, C26.1, C27.1, C31.2, C32.1, C40.1, C41.1, C42.1, C43.1, C44.1, C48.2, C49.1, C57.1, C58.1, C59.1, C60.1, C61.1, C65.2, C66.1, C74.1, C75.1, C76.1, C77.1, C78.1, C82.2, C83.1, C91.1, C92.1, C93.1, C94.1, C95.1, C99.2, C100.1, C125.1, C126.1, C127.1, C128.1, C129.1, C133.2, C134.1, C142.1, C143.1, C144.1, C145.1, C146.1, C150.2, C151.1, C159.1, C160.1, C161.1, C162.1, C163.1, C167.2, C168.1, U4.31 (VDD), U5.31 (VDD), U6.31 (VDD), U7.31 (VDD), U8.31 (VDD), U9.31 (VDD), U11.31 (VDD), U12.31 (VDD), U13.31 (VDD); also elsewhere on the board

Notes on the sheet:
low ESR
PIN_MODE = 0 : mode 0 PIN_MODE = 1 : mode 1 pull up interne

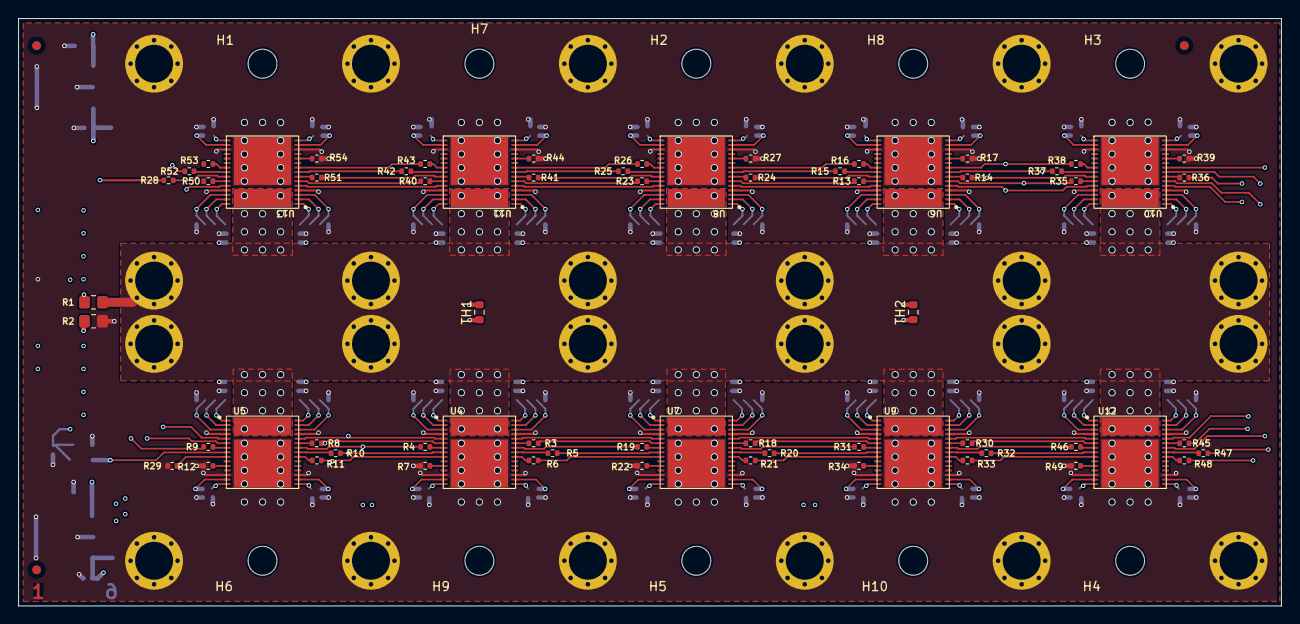
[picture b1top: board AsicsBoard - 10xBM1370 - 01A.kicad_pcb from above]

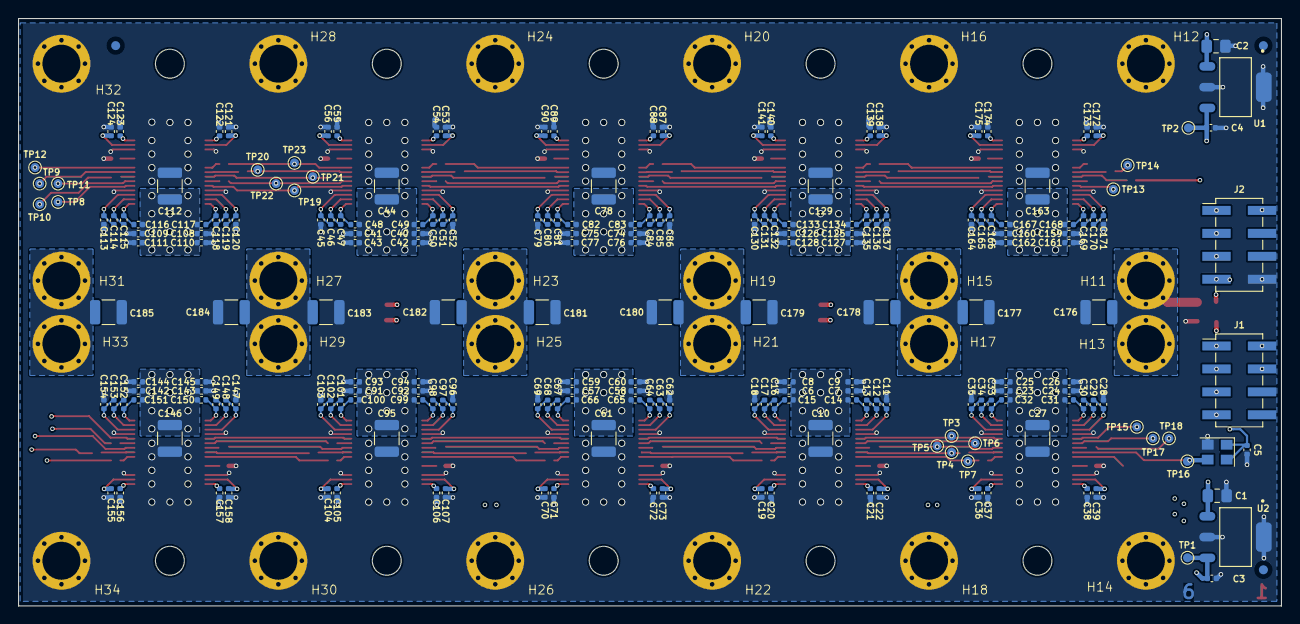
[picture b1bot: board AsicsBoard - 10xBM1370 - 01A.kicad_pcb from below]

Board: 6 copper layers, 139.8 x 65.0 mm, 319 parts (240 on the bottom side), 174 nets.
